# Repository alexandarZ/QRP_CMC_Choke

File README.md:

# QRP CMC Choke (PCB)

A PCB for a lightweight QRP common-mode choke — rated for **up to 10 W (SSB & CW)** or **5 W on FT8**.

---

### Overview
This common-mode choke (CMC) is built around an **Amidon FT82-43** core with a smaller **FT50-43** core nested inside it. The nested arrangement yields a compact, low-loss choke with improved high-frequency behaviour compared with a single core of the same outer size — an excellent choice for QRP use where minimal dissipation and a small form factor matter.

---

### Recommended cores
- **Outer core:** Amidon FT82-43 (or Fair-Rite equivalent 5943000601)  
- **Inner core:** Amidon / Fair-Rite FT50-43 (5943001101) placed inside the FT82-43  
- **Alternative (high bands only):** Würth 74270118 — performs well on higher frequencies but **not recommended below ~6 MHz**.

---

### Practical guidance
- For 40–10 m common-mode suppression, start with **~8–10 symmetrical turns** of 0.4mm2 enamelled wire, which are usually sufficient for typical QRP antenna setups.
- More turns increase common-mode impedance at lower frequencies, but also raise inter-winding capacitance — measure and adjust for your target bands.  
- Aim for **at least 20 dB of common-mode attenuation** across the target band where practical.  
- Target an **SWR as close to 1:1 as possible** after installing the choke; SWR below **1.5:1** is generally acceptable for most QRP uses.

**Wire & mechanical tips**
- Use enamelled copper wire sized appropriately for your power and mechanical needs — commonly 0.4–0.6 mm enamelled wire works well for QRP.  
- Keep pigtails and external leads short to avoid added series inductance.  
- Secure the nested cores mechanically with non-conductive tape or heat-shrink to prevent rotation or movement.

---

### How to test the CMC choke
Recommended guide (detailed):  
- Measuring common-mode choke performance — Lance Conry.  
  https://lance.conryclan.com/home/measuring-common-mode-choke-performance/

Quick checklist:
1. **Calibrate** your VNA for the measurement band.  
2. **Measure S21 parameter** in common-mode configuration to estimate CMC attenuation.
3. **Measure S21 parameter** in insertion loss configuration to estimate CMC insertion loss  
4. **Measure impedance / Z** vs frequency to verify target common-mode impedance.  
5. **Verify SWR** of your antenna/system with the choke installed to confirm no adverse effects.  

---

### Build results

| Band | CMC attenuation (dB) | Insertion loss (dB) | VSWR |
|---|---:|---:|---:|
| 80 m  | -29.63 dB | -0.09 dB | 1.008 |
| 40 m  | -32.78 dB | -0.21 dB | 1.014 |
| 30 m  | -33.96 dB | -0.29 dB | 1.019 |
| 20 m  | -34.39 dB | -0.32 dB | 1.026 |
| 17 m  | -34.16 dB | -0.34 dB | 1.037 |
| 15 m  | -33.45 dB | -0.33 dB | 1.047 |
| 12 m  | -32.24 dB | -0.34 dB | 1.059 |
| 10 m  | -30.62 dB | -0.35 dB | 1.073 |

## Build / Manufacture

I had a PCB manufactured for my project by **PCBWay** company and the experience was outstanding. The ordering process was straightforward, Gerber review options clear, and the price — considering the final product — is very economical. The build cost is low, yet the result feels far from cheap.
Quality of manufacture is top-tier: fine trace definition, neat vias, and excellent tolerance control. The board looks phenomenal — professional finish, crisp silkscreen, and clean markings. After assembly the choke behaved exactly as expected; the performance and results are of very high quality.
I recommend this company to anyone producing similar boards — great value for money and reliable results. Big thanks to the team for the fast, precise work and for helping bring this project to life.

**Gerber files:**  
FT82 version: `./gerbers/FT82_43_CMC_Choke.zip`  

### Recommended settings
Use the following manufacturing parameters when placing the order:

- **Board thickness:** `1.6 mm`  
- **Layers:** `2 (two-layer)`  
- **Material:** `FR-4`  
- **Copper weight:** `1 oz (35 µm)`  
- **Solder mask:** Chose your preferred

### 73s de YT3MW

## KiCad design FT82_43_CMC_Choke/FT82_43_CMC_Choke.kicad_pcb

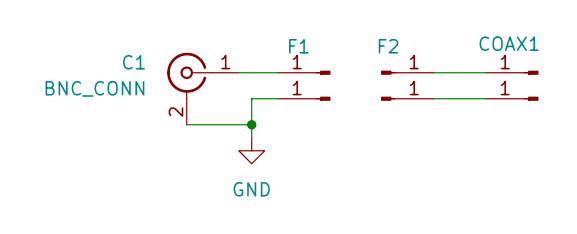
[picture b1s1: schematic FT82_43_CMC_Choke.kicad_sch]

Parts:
C1: BNC_CONN; BNC_Amphenol_B6252HB-NPP3G-50_Horizontal
COAX1: Conn_01x01_Pin; TestPoint_THTPad_2.5x2.5mm_Drill1.2mm
F1, F2: Conn_01x01_Pin; TestPoint_THTPad_2.5x2.5mm_Drill1.2mm
J1, J4, J6: Conn_01x01_Pin; TestPoint_THTPad_2.5x2.5mm_Drill1.2mm

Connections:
GND: C1.2 (Ext), F1.1
unnamed: C1.1 (In), J1.1
unnamed: COAX1.1, J4.1
unnamed: F2.1, J6.1

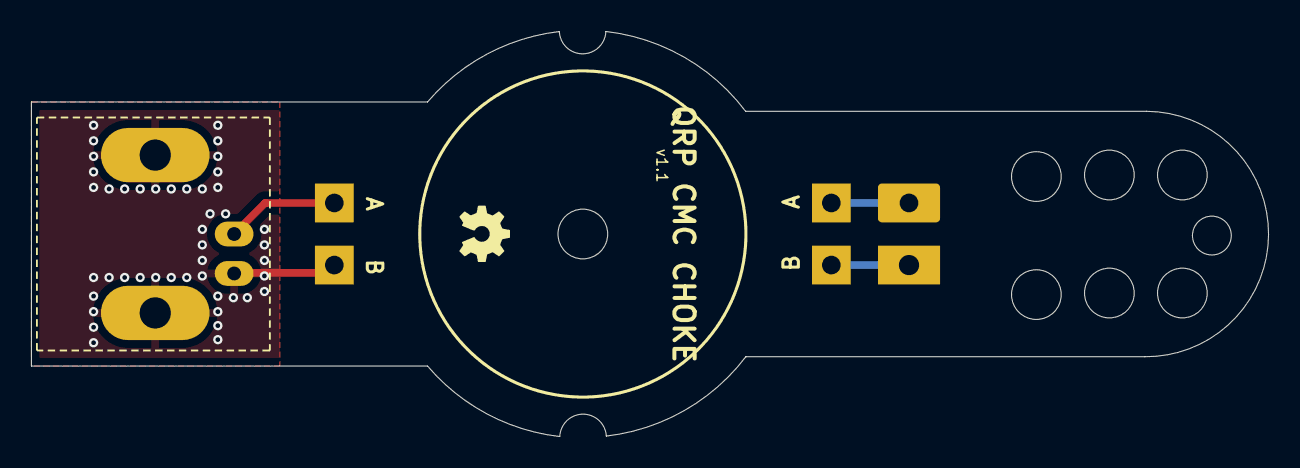
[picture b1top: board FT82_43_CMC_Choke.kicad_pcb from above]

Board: 2 copper layers, 79.6 x 26.1 mm, 7 parts (0 on the bottom side), 4 nets.

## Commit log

2026-01-01 Add LICENSE.md file
2026-01-01 PCB v1.1 and updates
2026-01-01 Gerber for PCB v1.1
2026-01-02 Add screenshot
2026-01-02 Update docs
2026-01-02 CMC Choke with FT114-43
2026-02-15 PCB v1_1 :)

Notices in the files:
FT82_43_CMC_Choke/FT82_43_CMC_Choke.kicad_pcb:
(CC BY-SA 4.0)
